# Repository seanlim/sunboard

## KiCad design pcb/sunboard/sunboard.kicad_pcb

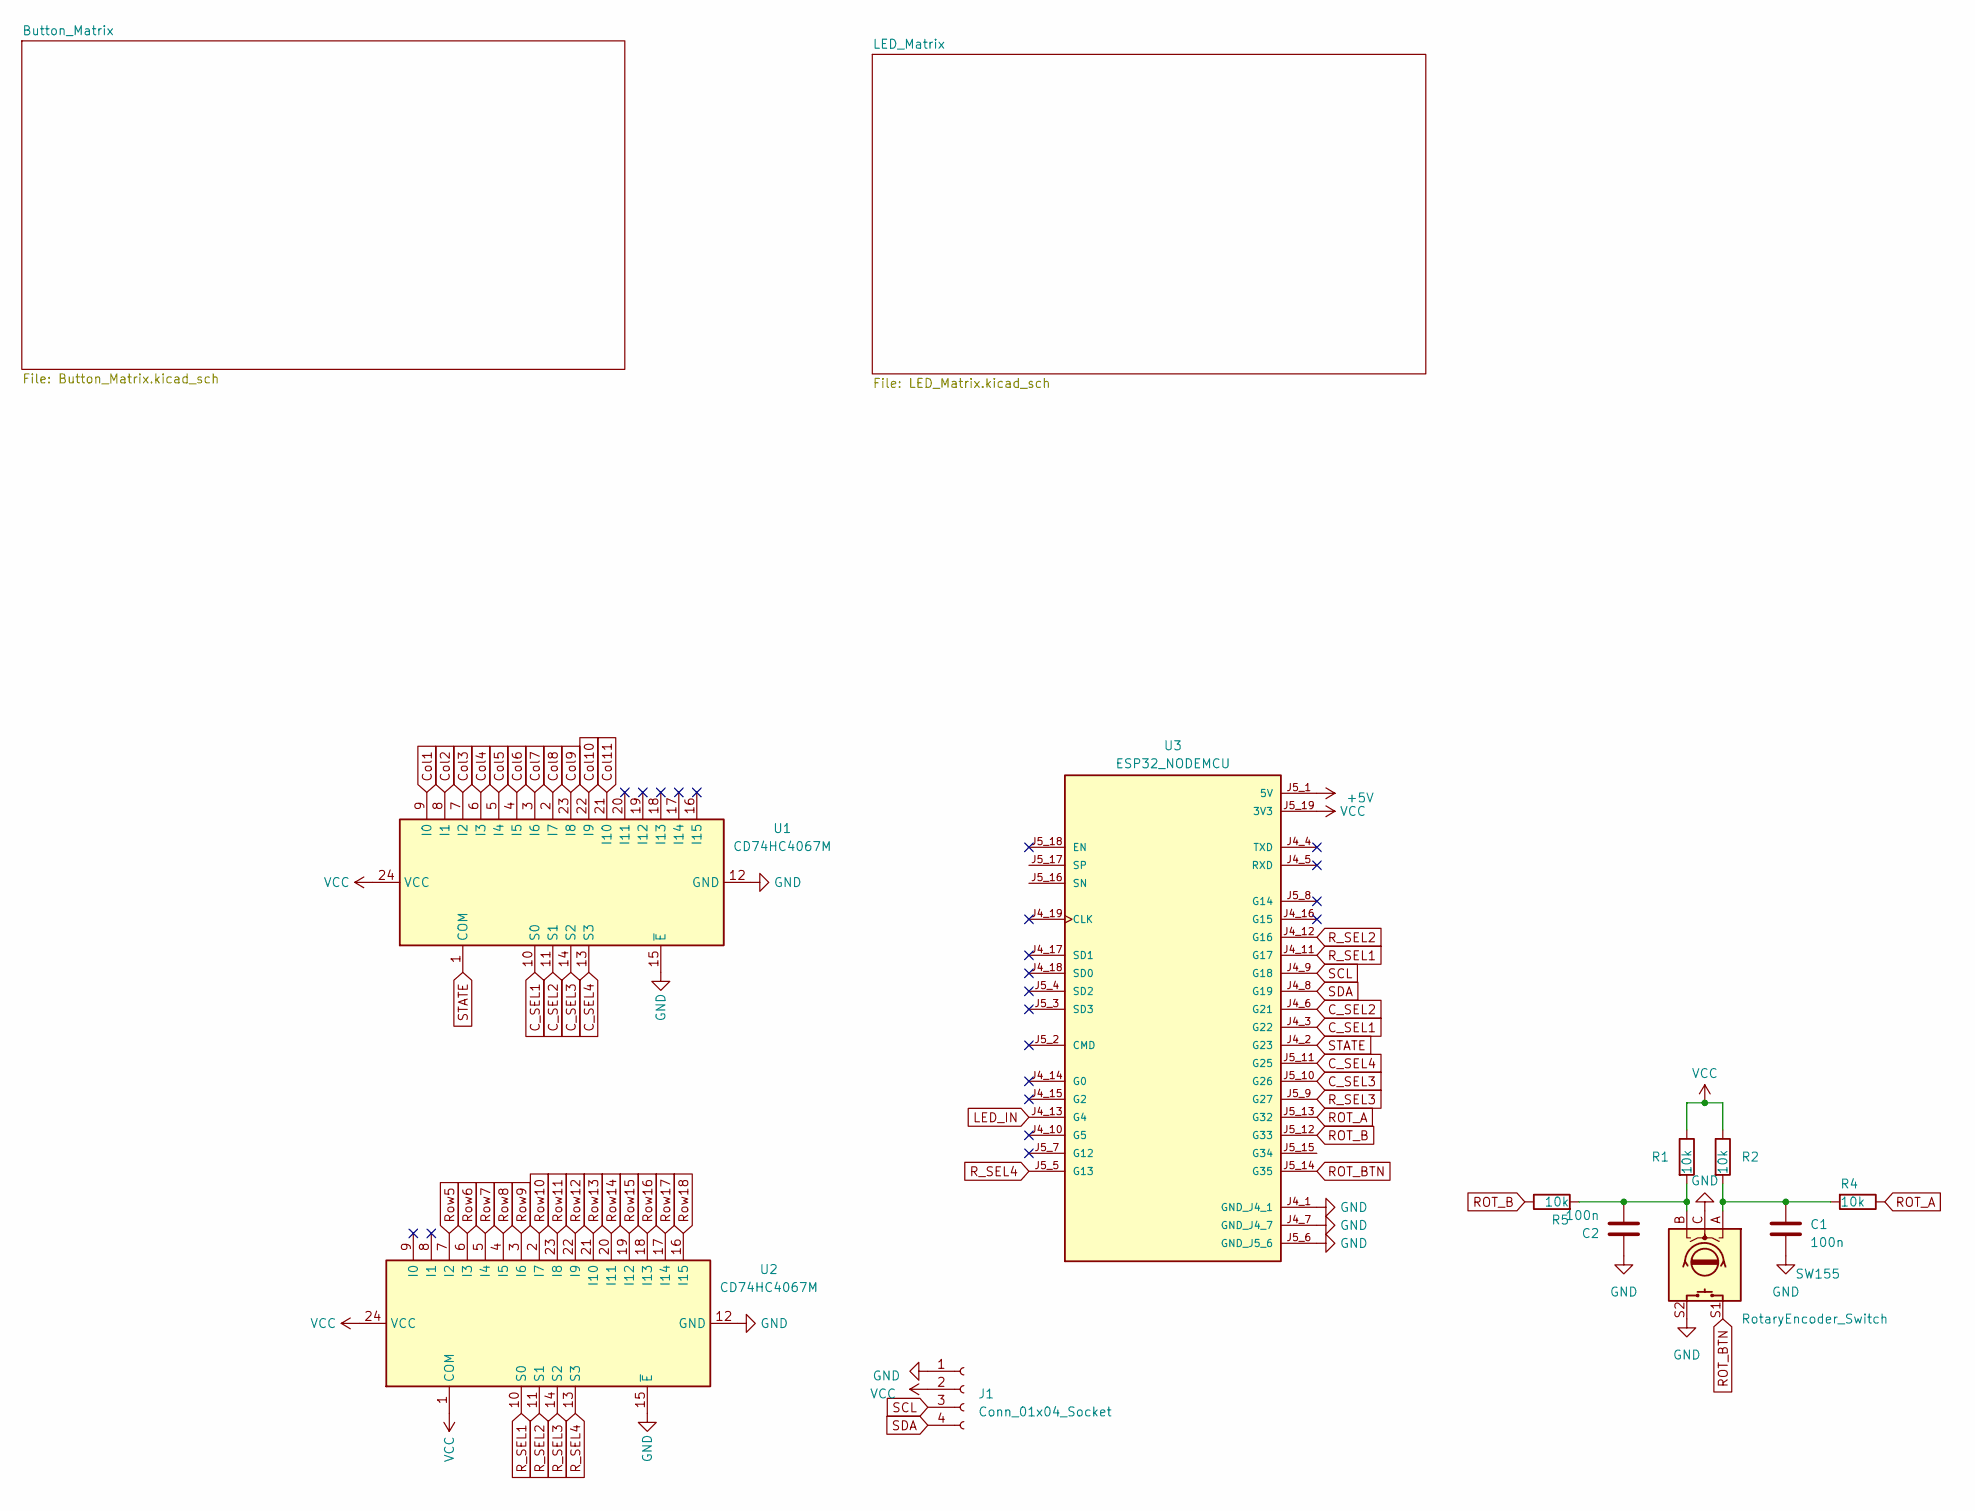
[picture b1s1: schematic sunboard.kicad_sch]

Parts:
C1, C2: 100n; C_0805_2012Metric; JLCPCB Part # C28233
J1: Conn_01x04_Socket; PinSocket_1x04_P2.54mm_Vertical
R1, R2, R4, R5: 10k; R_0805_2012Metric; JLCPCB Part # C17414
SW155: RotaryEncoder_Switch; RotaryEncoder_Alps_EC12E-Switch_Vertical_H20mm
U1, U2: CD74HC4067M; SOIC-24W_7.5x15.4mm_P1.27mm; JLCPCB Part # C496123
U3: ESP32_NODEMCU; MODULE_ESP32_NODEMCU

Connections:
+5V: U3.J5_1 (5V); also elsewhere on the board
C_SEL1: U1.14 (S2), U3.J5_10 (G26)
C_SEL2: U1.13 (S3), U3.J5_11 (G25)
C_SEL3: U1.10 (S0), U3.J4_3 (G22)
C_SEL4: U1.11 (S1), U3.J4_6 (G21)
Col1: U1.9 (I0); also elsewhere on the board
Col2: U1.8 (I1); also elsewhere on the board
Col3: U1.7 (I2); also elsewhere on the board
Col4: U1.6 (I3); also elsewhere on the board
Col5: U1.5 (I4); also elsewhere on the board
Col6: U1.4 (I5); also elsewhere on the board
Col7: U1.3 (I6); also elsewhere on the board
Col8: U1.2 (I7); also elsewhere on the board
Col9: U1.23 (I8); also elsewhere on the board
Col10: U1.22 (I9); also elsewhere on the board
Col11: U1.21 (I10); also elsewhere on the board
GND: C1.2, C2.1, J1.1, SW155.C, SW155.S2, U1.12 (GND), U1.15 (~E), U2.12 (GND), U2.15 (~E), U3.J4_1 (GND_J4_1), U3.J4_7 (GND_J4_7), U3.J5_6 (GND_J5_6); also elsewhere on the board
LED_IN: U3.J4_13 (G4); also elsewhere on the board
unnamed: C1.1, R2.2, R4.2, SW155.A
unnamed: C2.2, R1.2, R5.2, SW155.B
ROT_A: R4.1, U3.J5_13 (G32)
ROT_B: R5.1, U3.J5_12 (G33)
ROT_BTN: SW155.S1, U3.J5_14 (G35)
R_SEL1: U2.10 (S0), U3.J4_11 (G17)
R_SEL2: U2.11 (S1), U3.J4_12 (G16)
R_SEL3: U2.14 (S2), U3.J5_9 (G27)
R_SEL4: U2.13 (S3), U3.J5_5 (G13)
Row5: U2.7 (I2); also elsewhere on the board
Row6: U2.6 (I3); also elsewhere on the board
Row7: U2.5 (I4); also elsewhere on the board
Row8: U2.4 (I5); also elsewhere on the board
Row9: U2.3 (I6); also elsewhere on the board
Row10: U2.2 (I7); also elsewhere on the board
Row11: U2.23 (I8); also elsewhere on the board
Row12: U2.22 (I9); also elsewhere on the board
Row13: U2.21 (I10); also elsewhere on the board
Row14: U2.20 (I11); also elsewhere on the board
Row15: U2.19 (I12); also elsewhere on the board
Row16: U2.18 (I13); also elsewhere on the board
Row17: U2.17 (I14); also elsewhere on the board
Row18: U2.16 (I15); also elsewhere on the board
SCL: J1.3, U3.J4_9 (G18)
SDA: J1.4, U3.J4_8 (G19)
STATE: U1.1 (COM), U3.J4_2 (G23)
VCC: J1.2, R1.1, R2.1, U1.24 (VCC), U2.1 (COM), U2.24 (VCC), U3.J5_19 (3V3)

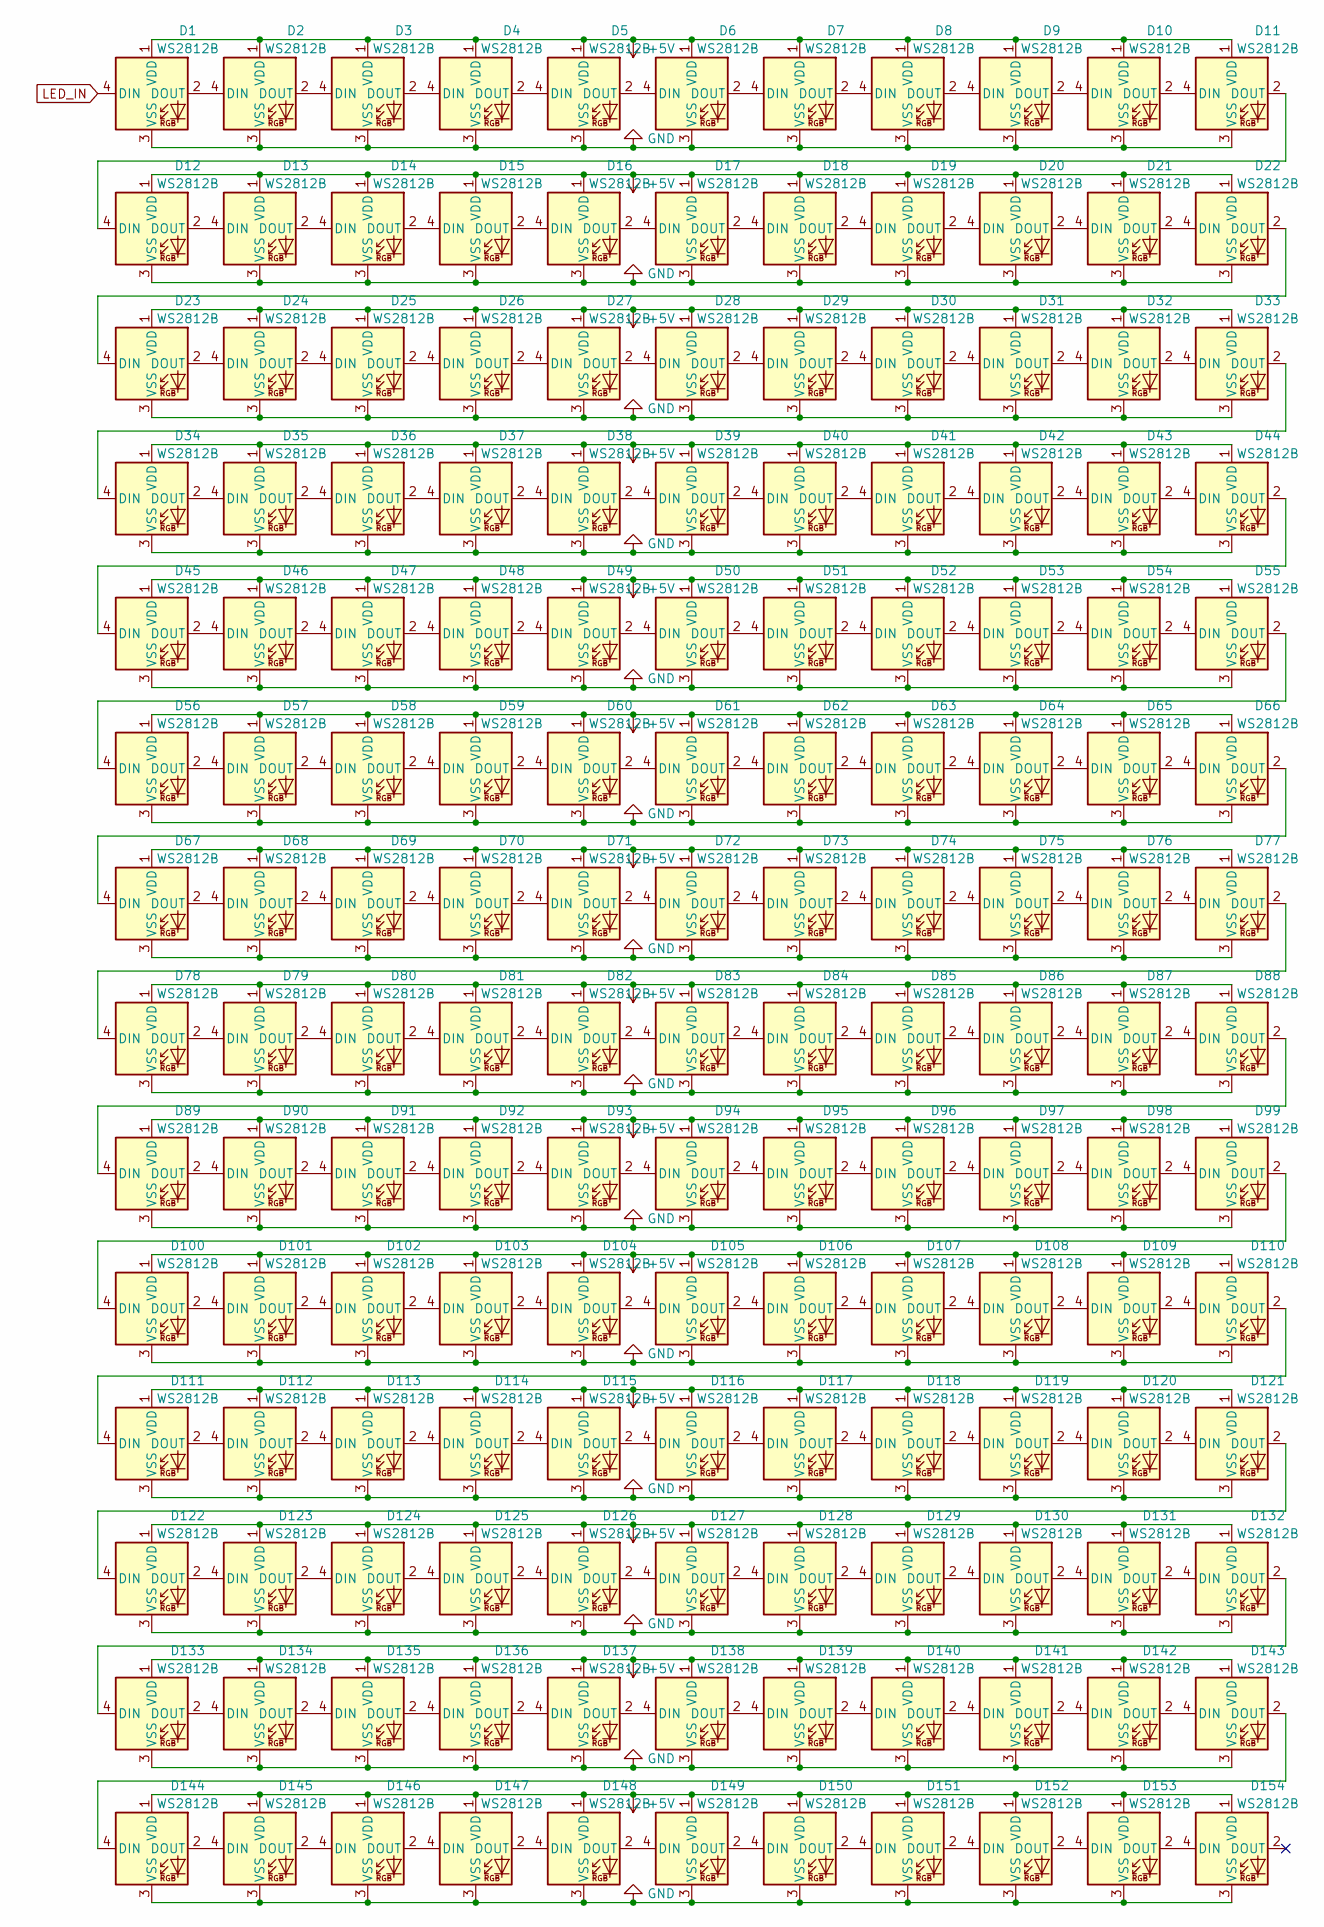
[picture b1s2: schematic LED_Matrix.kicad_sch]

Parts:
D1, D2, D3, D4, D5, D6, D7, D8, D9, D10, D11, D12, D13, D14, D15, D16, D17, D18, D19, D20, D21, D22, D23, D24, D25, D26, D27, D28, D29, D30, D31, D32, D33, D34, D35, D36, D37, D38, D39, D40, D41, D42, D43, D44, D45, D46, D47, D48, D49, D50, D51, D52, D53, D54, D55, D56, D57, D58, D59, D60, D61, D62, D63, D64, D65, D66, D67, D68, D69, D70, D71, D72, D73, D74, D75, D76, D77, D78, D79, D80, D81, D82, D83, D84, D85, D86, D87, D88, D89, D90, D91, D92, D93, D94, D95, D96, D97, D98, D99, D100, D101, D102, D103, D104, D105, D106, D107, D108, D109, D110, D111, D112, D113, D114, D115, D116, D117, D118, D119, D120, D121, D122, D123, D124, D125, D126, D127, D128, D129, D130, D131, D132, D133, D134, D135, D136, D137, D138, D139, D140, D141, D142, D143, D144, D145, D146, D147, D148, D149, D150, D151, D152, D153, D154: WS2812B; LED_WS2812B_PLCC4_5.0x5.0mm_P3.2mm; JLCPCB Part # C2843785

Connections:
+5V: D1.1 (VDD), D2.1 (VDD), D3.1 (VDD), D4.1 (VDD), D5.1 (VDD), D6.1 (VDD), D7.1 (VDD), D8.1 (VDD), D9.1 (VDD), D10.1 (VDD), D11.1 (VDD), D12.1 (VDD), D13.1 (VDD), D14.1 (VDD), D15.1 (VDD), D16.1 (VDD), D17.1 (VDD), D18.1 (VDD), D19.1 (VDD), D20.1 (VDD), D21.1 (VDD), D22.1 (VDD), D23.1 (VDD), D24.1 (VDD), D25.1 (VDD), D26.1 (VDD), D27.1 (VDD), D28.1 (VDD), D29.1 (VDD), D30.1 (VDD), D31.1 (VDD), D32.1 (VDD), D33.1 (VDD), D34.1 (VDD), D35.1 (VDD), D36.1 (VDD), D37.1 (VDD), D38.1 (VDD), D39.1 (VDD), D40.1 (VDD), D41.1 (VDD), D42.1 (VDD), D43.1 (VDD), D44.1 (VDD), D45.1 (VDD), D46.1 (VDD), D47.1 (VDD), D48.1 (VDD), D49.1 (VDD), D50.1 (VDD), D51.1 (VDD), D52.1 (VDD), D53.1 (VDD), D54.1 (VDD), D55.1 (VDD), D56.1 (VDD), D57.1 (VDD), D58.1 (VDD), D59.1 (VDD), D60.1 (VDD), D61.1 (VDD), D62.1 (VDD), D63.1 (VDD), D64.1 (VDD), D65.1 (VDD), D66.1 (VDD), D67.1 (VDD), D68.1 (VDD), D69.1 (VDD), D70.1 (VDD), D71.1 (VDD), D72.1 (VDD), D73.1 (VDD), D74.1 (VDD), D75.1 (VDD), D76.1 (VDD), D77.1 (VDD), D78.1 (VDD), D79.1 (VDD), D80.1 (VDD), D81.1 (VDD), D82.1 (VDD), D83.1 (VDD), D84.1 (VDD), D85.1 (VDD), D86.1 (VDD), D87.1 (VDD), D88.1 (VDD), D89.1 (VDD), D90.1 (VDD), D91.1 (VDD), D92.1 (VDD), D93.1 (VDD), D94.1 (VDD), D95.1 (VDD), D96.1 (VDD), D97.1 (VDD), D98.1 (VDD), D99.1 (VDD), D100.1 (VDD), D101.1 (VDD), D102.1 (VDD), D103.1 (VDD), D104.1 (VDD), D105.1 (VDD), D106.1 (VDD), D107.1 (VDD), D108.1 (VDD), D109.1 (VDD), D110.1 (VDD), D111.1 (VDD), D112.1 (VDD), D113.1 (VDD), D114.1 (VDD), D115.1 (VDD), D116.1 (VDD), D117.1 (VDD), D118.1 (VDD), D119.1 (VDD), D120.1 (VDD), D121.1 (VDD), D122.1 (VDD), D123.1 (VDD), D124.1 (VDD), D125.1 (VDD), D126.1 (VDD), D127.1 (VDD), D128.1 (VDD), D129.1 (VDD), D130.1 (VDD), D131.1 (VDD), D132.1 (VDD), D133.1 (VDD), D134.1 (VDD), D135.1 (VDD), D136.1 (VDD), D137.1 (VDD), D138.1 (VDD), D139.1 (VDD), D140.1 (VDD), D141.1 (VDD), D142.1 (VDD), D143.1 (VDD), D144.1 (VDD), D145.1 (VDD), D146.1 (VDD), D147.1 (VDD), D148.1 (VDD), D149.1 (VDD), D150.1 (VDD), D151.1 (VDD), D152.1 (VDD), D153.1 (VDD), D154.1 (VDD); also elsewhere on the board
GND: D1.3 (VSS), D2.3 (VSS), D3.3 (VSS), D4.3 (VSS), D5.3 (VSS), D6.3 (VSS), D7.3 (VSS), D8.3 (VSS), D9.3 (VSS), D10.3 (VSS), D11.3 (VSS), D12.3 (VSS), D13.3 (VSS), D14.3 (VSS), D15.3 (VSS), D16.3 (VSS), D17.3 (VSS), D18.3 (VSS), D19.3 (VSS), D20.3 (VSS), D21.3 (VSS), D22.3 (VSS), D23.3 (VSS), D24.3 (VSS), D25.3 (VSS), D26.3 (VSS), D27.3 (VSS), D28.3 (VSS), D29.3 (VSS), D30.3 (VSS), D31.3 (VSS), D32.3 (VSS), D33.3 (VSS), D34.3 (VSS), D35.3 (VSS), D36.3 (VSS), D37.3 (VSS), D38.3 (VSS), D39.3 (VSS), D40.3 (VSS), D41.3 (VSS), D42.3 (VSS), D43.3 (VSS), D44.3 (VSS), D45.3 (VSS), D46.3 (VSS), D47.3 (VSS), D48.3 (VSS), D49.3 (VSS), D50.3 (VSS), D51.3 (VSS), D52.3 (VSS), D53.3 (VSS), D54.3 (VSS), D55.3 (VSS), D56.3 (VSS), D57.3 (VSS), D58.3 (VSS), D59.3 (VSS), D60.3 (VSS), D61.3 (VSS), D62.3 (VSS), D63.3 (VSS), D64.3 (VSS), D65.3 (VSS), D66.3 (VSS), D67.3 (VSS), D68.3 (VSS), D69.3 (VSS), D70.3 (VSS), D71.3 (VSS), D72.3 (VSS), D73.3 (VSS), D74.3 (VSS), D75.3 (VSS), D76.3 (VSS), D77.3 (VSS), D78.3 (VSS), D79.3 (VSS), D80.3 (VSS), D81.3 (VSS), D82.3 (VSS), D83.3 (VSS), D84.3 (VSS), D85.3 (VSS), D86.3 (VSS), D87.3 (VSS), D88.3 (VSS), D89.3 (VSS), D90.3 (VSS), D91.3 (VSS), D92.3 (VSS), D93.3 (VSS), D94.3 (VSS), D95.3 (VSS), D96.3 (VSS), D97.3 (VSS), D98.3 (VSS), D99.3 (VSS), D100.3 (VSS), D101.3 (VSS), D102.3 (VSS), D103.3 (VSS), D104.3 (VSS), D105.3 (VSS), D106.3 (VSS), D107.3 (VSS), D108.3 (VSS), D109.3 (VSS), D110.3 (VSS), D111.3 (VSS), D112.3 (VSS), D113.3 (VSS), D114.3 (VSS), D115.3 (VSS), D116.3 (VSS), D117.3 (VSS), D118.3 (VSS), D119.3 (VSS), D120.3 (VSS), D121.3 (VSS), D122.3 (VSS), D123.3 (VSS), D124.3 (VSS), D125.3 (VSS), D126.3 (VSS), D127.3 (VSS), D128.3 (VSS), D129.3 (VSS), D130.3 (VSS), D131.3 (VSS), D132.3 (VSS), D133.3 (VSS), D134.3 (VSS), D135.3 (VSS), D136.3 (VSS), D137.3 (VSS), D138.3 (VSS), D139.3 (VSS), D140.3 (VSS), D141.3 (VSS), D142.3 (VSS), D143.3 (VSS), D144.3 (VSS), D145.3 (VSS), D146.3 (VSS), D147.3 (VSS), D148.3 (VSS), D149.3 (VSS), D150.3 (VSS), D151.3 (VSS), D152.3 (VSS), D153.3 (VSS), D154.3 (VSS); also elsewhere on the board
LED_IN: D1.4 (DIN); also elsewhere on the board
unnamed: D1.2 (DOUT), D2.4 (DIN)
unnamed: D2.2 (DOUT), D3.4 (DIN)
unnamed: D3.2 (DOUT), D4.4 (DIN)
unnamed: D4.2 (DOUT), D5.4 (DIN)
unnamed: D5.2 (DOUT), D6.4 (DIN)
unnamed: D6.2 (DOUT), D7.4 (DIN)
unnamed: D7.2 (DOUT), D8.4 (DIN)
unnamed: D8.2 (DOUT), D9.4 (DIN)
unnamed: D9.2 (DOUT), D10.4 (DIN)
unnamed: D10.2 (DOUT), D11.4 (DIN)
unnamed: D11.2 (DOUT), D12.4 (DIN)
unnamed: D12.2 (DOUT), D13.4 (DIN)
unnamed: D13.2 (DOUT), D14.4 (DIN)
unnamed: D14.2 (DOUT), D15.4 (DIN)
unnamed: D15.2 (DOUT), D16.4 (DIN)
unnamed: D16.2 (DOUT), D17.4 (DIN)
unnamed: D17.2 (DOUT), D18.4 (DIN)
unnamed: D18.2 (DOUT), D19.4 (DIN)
unnamed: D19.2 (DOUT), D20.4 (DIN)
unnamed: D20.2 (DOUT), D21.4 (DIN)
unnamed: D21.2 (DOUT), D22.4 (DIN)
unnamed: D22.2 (DOUT), D23.4 (DIN)
unnamed: D23.2 (DOUT), D24.4 (DIN)
unnamed: D24.2 (DOUT), D25.4 (DIN)
unnamed: D25.2 (DOUT), D26.4 (DIN)
unnamed: D26.2 (DOUT), D27.4 (DIN)
unnamed: D27.2 (DOUT), D28.4 (DIN)
unnamed: D28.2 (DOUT), D29.4 (DIN)
unnamed: D29.2 (DOUT), D30.4 (DIN)
unnamed: D30.2 (DOUT), D31.4 (DIN)
unnamed: D31.2 (DOUT), D32.4 (DIN)
unnamed: D32.2 (DOUT), D33.4 (DIN)
unnamed: D33.2 (DOUT), D34.4 (DIN)
unnamed: D34.2 (DOUT), D35.4 (DIN)
unnamed: D35.2 (DOUT), D36.4 (DIN)
unnamed: D36.2 (DOUT), D37.4 (DIN)
unnamed: D37.2 (DOUT), D38.4 (DIN)
unnamed: D38.2 (DOUT), D39.4 (DIN)
unnamed: D39.2 (DOUT), D40.4 (DIN)
unnamed: D40.2 (DOUT), D41.4 (DIN)
unnamed: D41.2 (DOUT), D42.4 (DIN)
unnamed: D42.2 (DOUT), D43.4 (DIN)
unnamed: D43.2 (DOUT), D44.4 (DIN)
unnamed: D44.2 (DOUT), D45.4 (DIN)
unnamed: D45.2 (DOUT), D46.4 (DIN)
unnamed: D46.2 (DOUT), D47.4 (DIN)
unnamed: D47.2 (DOUT), D48.4 (DIN)
unnamed: D48.2 (DOUT), D49.4 (DIN)
unnamed: D49.2 (DOUT), D50.4 (DIN)
unnamed: D50.2 (DOUT), D51.4 (DIN)
unnamed: D51.2 (DOUT), D52.4 (DIN)
unnamed: D52.2 (DOUT), D53.4 (DIN)
unnamed: D53.2 (DOUT), D54.4 (DIN)
unnamed: D54.2 (DOUT), D55.4 (DIN)
unnamed: D55.2 (DOUT), D56.4 (DIN)
unnamed: D56.2 (DOUT), D57.4 (DIN)
unnamed: D57.2 (DOUT), D58.4 (DIN)
unnamed: D58.2 (DOUT), D59.4 (DIN)
unnamed: D59.2 (DOUT), D60.4 (DIN)
unnamed: D60.2 (DOUT), D61.4 (DIN)
unnamed: D61.2 (DOUT), D62.4 (DIN)
unnamed: D62.2 (DOUT), D63.4 (DIN)
unnamed: D63.2 (DOUT), D64.4 (DIN)
unnamed: D64.2 (DOUT), D65.4 (DIN)
unnamed: D65.2 (DOUT), D66.4 (DIN)
unnamed: D66.2 (DOUT), D67.4 (DIN)
unnamed: D67.2 (DOUT), D68.4 (DIN)
unnamed: D68.2 (DOUT), D69.4 (DIN)
unnamed: D69.2 (DOUT), D70.4 (DIN)
unnamed: D70.2 (DOUT), D71.4 (DIN)
unnamed: D71.2 (DOUT), D72.4 (DIN)
unnamed: D72.2 (DOUT), D73.4 (DIN)
unnamed: D73.2 (DOUT), D74.4 (DIN)
unnamed: D74.2 (DOUT), D75.4 (DIN)
unnamed: D75.2 (DOUT), D76.4 (DIN)
unnamed: D76.2 (DOUT), D77.4 (DIN)
unnamed: D77.2 (DOUT), D78.4 (DIN)
unnamed: D78.2 (DOUT), D79.4 (DIN)
unnamed: D79.2 (DOUT), D80.4 (DIN)
unnamed: D80.2 (DOUT), D81.4 (DIN)
unnamed: D81.2 (DOUT), D82.4 (DIN)
unnamed: D82.2 (DOUT), D83.4 (DIN)
unnamed: D83.2 (DOUT), D84.4 (DIN)
unnamed: D84.2 (DOUT), D85.4 (DIN)
unnamed: D85.2 (DOUT), D86.4 (DIN)
unnamed: D86.2 (DOUT), D87.4 (DIN)
unnamed: D87.2 (DOUT), D88.4 (DIN)
unnamed: D88.2 (DOUT), D89.4 (DIN)
unnamed: D89.2 (DOUT), D90.4 (DIN)
unnamed: D90.2 (DOUT), D91.4 (DIN)
unnamed: D91.2 (DOUT), D92.4 (DIN)
unnamed: D92.2 (DOUT), D93.4 (DIN)
unnamed: D93.2 (DOUT), D94.4 (DIN)
unnamed: D94.2 (DOUT), D95.4 (DIN)
unnamed: D95.2 (DOUT), D96.4 (DIN)
unnamed: D96.2 (DOUT), D97.4 (DIN)
unnamed: D97.2 (DOUT), D98.4 (DIN)
unnamed: D98.2 (DOUT), D99.4 (DIN)
unnamed: D99.2 (DOUT), D100.4 (DIN)
unnamed: D100.2 (DOUT), D101.4 (DIN)
unnamed: D101.2 (DOUT), D102.4 (DIN)
unnamed: D102.2 (DOUT), D103.4 (DIN)
unnamed: D103.2 (DOUT), D104.4 (DIN)
unnamed: D104.2 (DOUT), D105.4 (DIN)
unnamed: D105.2 (DOUT), D106.4 (DIN)
unnamed: D106.2 (DOUT), D107.4 (DIN)
unnamed: D107.2 (DOUT), D108.4 (DIN)
unnamed: D108.2 (DOUT), D109.4 (DIN)
unnamed: D109.2 (DOUT), D110.4 (DIN)
unnamed: D110.2 (DOUT), D111.4 (DIN)
unnamed: D111.2 (DOUT), D112.4 (DIN)
unnamed: D112.2 (DOUT), D113.4 (DIN)
unnamed: D113.2 (DOUT), D114.4 (DIN)
unnamed: D114.2 (DOUT), D115.4 (DIN)
unnamed: D115.2 (DOUT), D116.4 (DIN)
unnamed: D116.2 (DOUT), D117.4 (DIN)
unnamed: D117.2 (DOUT), D118.4 (DIN)
unnamed: D118.2 (DOUT), D119.4 (DIN)
unnamed: D119.2 (DOUT), D120.4 (DIN)
unnamed: D120.2 (DOUT), D121.4 (DIN)
unnamed: D121.2 (DOUT), D122.4 (DIN)
unnamed: D122.2 (DOUT), D123.4 (DIN)
unnamed: D123.2 (DOUT), D124.4 (DIN)
unnamed: D124.2 (DOUT), D125.4 (DIN)
unnamed: D125.2 (DOUT), D126.4 (DIN)
unnamed: D126.2 (DOUT), D127.4 (DIN)
unnamed: D127.2 (DOUT), D128.4 (DIN)
unnamed: D128.2 (DOUT), D129.4 (DIN)
unnamed: D129.2 (DOUT), D130.4 (DIN)
unnamed: D130.2 (DOUT), D131.4 (DIN)
unnamed: D131.2 (DOUT), D132.4 (DIN)
unnamed: D132.2 (DOUT), D133.4 (DIN)
unnamed: D133.2 (DOUT), D134.4 (DIN)
unnamed: D134.2 (DOUT), D135.4 (DIN)
unnamed: D135.2 (DOUT), D136.4 (DIN)
unnamed: D136.2 (DOUT), D137.4 (DIN)
unnamed: D137.2 (DOUT), D138.4 (DIN)
unnamed: D138.2 (DOUT), D139.4 (DIN)
unnamed: D139.2 (DOUT), D140.4 (DIN)
unnamed: D140.2 (DOUT), D141.4 (DIN)
unnamed: D141.2 (DOUT), D142.4 (DIN)
unnamed: D142.2 (DOUT), D143.4 (DIN)
unnamed: D143.2 (DOUT), D144.4 (DIN)
unnamed: D144.2 (DOUT), D145.4 (DIN)
unnamed: D145.2 (DOUT), D146.4 (DIN)
unnamed: D146.2 (DOUT), D147.4 (DIN)
unnamed: D147.2 (DOUT), D148.4 (DIN)
unnamed: D148.2 (DOUT), D149.4 (DIN)
unnamed: D149.2 (DOUT), D150.4 (DIN)
unnamed: D150.2 (DOUT), D151.4 (DIN)
unnamed: D151.2 (DOUT), D152.4 (DIN)
unnamed: D152.2 (DOUT), D153.4 (DIN)
unnamed: D153.2 (DOUT), D154.4 (DIN)

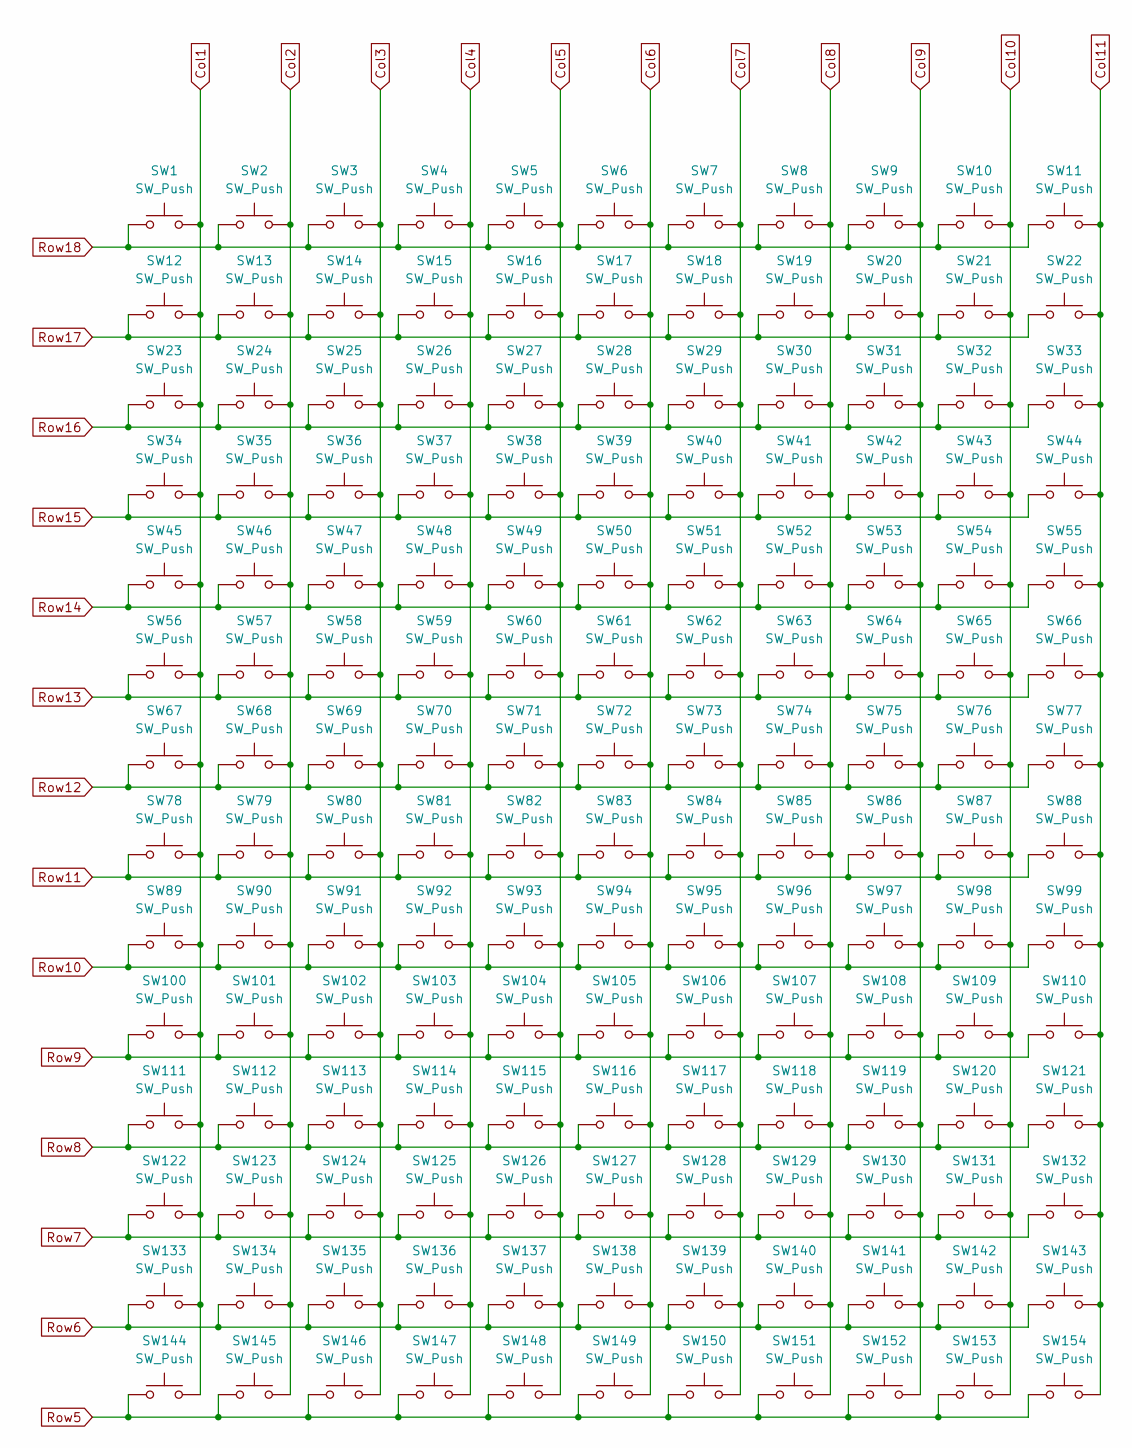
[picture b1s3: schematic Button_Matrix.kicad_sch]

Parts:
SW1, SW2, SW3, SW4, SW5, SW6, SW7, SW8, SW9, SW10, SW11, SW12, SW13, SW14, SW15, SW16, SW17, SW18, SW19, SW20, SW21, SW22, SW23, SW24, SW25, SW26, SW27, SW28, SW29, SW30, SW31, SW32, SW33, SW34, SW35, SW36, SW37, SW38, SW39, SW40, SW41, SW42, SW43, SW44, SW45, SW46, SW47, SW48, SW49, SW50, SW51, SW52, SW53, SW54, SW55, SW56, SW57, SW58, SW59, SW60, SW61, SW62, SW63, SW64, SW65, SW66, SW67, SW68, SW69, SW70, SW71, SW72, SW73, SW74, SW75, SW76, SW77, SW78, SW79, SW80, SW81, SW82, SW83, SW84, SW85, SW86, SW87, SW88, SW89, SW90, SW91, SW92, SW93, SW94, SW95, SW96, SW97, SW98, SW99, SW100, SW101, SW102, SW103, SW104, SW105, SW106, SW107, SW108, SW109, SW110, SW111, SW112, SW113, SW114, SW115, SW116, SW117, SW118, SW119, SW120, SW121, SW122, SW123, SW124, SW125, SW126, SW127, SW128, SW129, SW130, SW131, SW132, SW133, SW134, SW135, SW136, SW137, SW138, SW139, SW140, SW141, SW142, SW143, SW144, SW145, SW146, SW147, SW148, SW149, SW150, SW151, SW152, SW153, SW154: SW_Push; SW_Push_1P1T_NO_6x6mm_H9.5mm; JLCPCB Part # C455109

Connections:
Col1: SW1.2, SW12.2, SW23.2, SW34.2, SW45.2, SW56.2, SW67.2, SW78.2, SW89.2, SW100.2, SW111.2, SW122.2, SW133.2, SW144.2; also elsewhere on the board
Col2: SW2.2, SW13.2, SW24.2, SW35.2, SW46.2, SW57.2, SW68.2, SW79.2, SW90.2, SW101.2, SW112.2, SW123.2, SW134.2, SW145.2; also elsewhere on the board
Col3: SW3.2, SW14.2, SW25.2, SW36.2, SW47.2, SW58.2, SW69.2, SW80.2, SW91.2, SW102.2, SW113.2, SW124.2, SW135.2, SW146.2; also elsewhere on the board
Col4: SW4.2, SW15.2, SW26.2, SW37.2, SW48.2, SW59.2, SW70.2, SW81.2, SW92.2, SW103.2, SW114.2, SW125.2, SW136.2, SW147.2; also elsewhere on the board
Col5: SW5.2, SW16.2, SW27.2, SW38.2, SW49.2, SW60.2, SW71.2, SW82.2, SW93.2, SW104.2, SW115.2, SW126.2, SW137.2, SW148.2; also elsewhere on the board
Col6: SW6.2, SW17.2, SW28.2, SW39.2, SW50.2, SW61.2, SW72.2, SW83.2, SW94.2, SW105.2, SW116.2, SW127.2, SW138.2, SW149.2; also elsewhere on the board
Col7: SW7.2, SW18.2, SW29.2, SW40.2, SW51.2, SW62.2, SW73.2, SW84.2, SW95.2, SW106.2, SW117.2, SW128.2, SW139.2, SW150.2; also elsewhere on the board
Col8: SW8.2, SW19.2, SW30.2, SW41.2, SW52.2, SW63.2, SW74.2, SW85.2, SW96.2, SW107.2, SW118.2, SW129.2, SW140.2, SW151.2; also elsewhere on the board
Col9: SW9.2, SW20.2, SW31.2, SW42.2, SW53.2, SW64.2, SW75.2, SW86.2, SW97.2, SW108.2, SW119.2, SW130.2, SW141.2, SW152.2; also elsewhere on the board
Col10: SW10.2, SW21.2, SW32.2, SW43.2, SW54.2, SW65.2, SW76.2, SW87.2, SW98.2, SW109.2, SW120.2, SW131.2, SW142.2, SW153.2; also elsewhere on the board
Col11: SW11.2, SW22.2, SW33.2, SW44.2, SW55.2, SW66.2, SW77.2, SW88.2, SW99.2, SW110.2, SW121.2, SW132.2, SW143.2, SW154.2; also elsewhere on the board
Row5: SW144.1, SW145.1, SW146.1, SW147.1, SW148.1, SW149.1, SW150.1, SW151.1, SW152.1, SW153.1, SW154.1; also elsewhere on the board
Row6: SW133.1, SW134.1, SW135.1, SW136.1, SW137.1, SW138.1, SW139.1, SW140.1, SW141.1, SW142.1, SW143.1; also elsewhere on the board
Row7: SW122.1, SW123.1, SW124.1, SW125.1, SW126.1, SW127.1, SW128.1, SW129.1, SW130.1, SW131.1, SW132.1; also elsewhere on the board
Row8: SW111.1, SW112.1, SW113.1, SW114.1, SW115.1, SW116.1, SW117.1, SW118.1, SW119.1, SW120.1, SW121.1; also elsewhere on the board
Row9: SW100.1, SW101.1, SW102.1, SW103.1, SW104.1, SW105.1, SW106.1, SW107.1, SW108.1, SW109.1, SW110.1; also elsewhere on the board
Row10: SW89.1, SW90.1, SW91.1, SW92.1, SW93.1, SW94.1, SW95.1, SW96.1, SW97.1, SW98.1, SW99.1; also elsewhere on the board
Row11: SW78.1, SW79.1, SW80.1, SW81.1, SW82.1, SW83.1, SW84.1, SW85.1, SW86.1, SW87.1, SW88.1; also elsewhere on the board
Row12: SW67.1, SW68.1, SW69.1, SW70.1, SW71.1, SW72.1, SW73.1, SW74.1, SW75.1, SW76.1, SW77.1; also elsewhere on the board
Row13: SW56.1, SW57.1, SW58.1, SW59.1, SW60.1, SW61.1, SW62.1, SW63.1, SW64.1, SW65.1, SW66.1; also elsewhere on the board
Row14: SW45.1, SW46.1, SW47.1, SW48.1, SW49.1, SW50.1, SW51.1, SW52.1, SW53.1, SW54.1, SW55.1; also elsewhere on the board
Row15: SW34.1, SW35.1, SW36.1, SW37.1, SW38.1, SW39.1, SW40.1, SW41.1, SW42.1, SW43.1, SW44.1; also elsewhere on the board
Row16: SW23.1, SW24.1, SW25.1, SW26.1, SW27.1, SW28.1, SW29.1, SW30.1, SW31.1, SW32.1, SW33.1; also elsewhere on the board
Row17: SW12.1, SW13.1, SW14.1, SW15.1, SW16.1, SW17.1, SW18.1, SW19.1, SW20.1, SW21.1, SW22.1; also elsewhere on the board
Row18: SW1.1, SW2.1, SW3.1, SW4.1, SW5.1, SW6.1, SW7.1, SW8.1, SW9.1, SW10.1, SW11.1; also elsewhere on the board

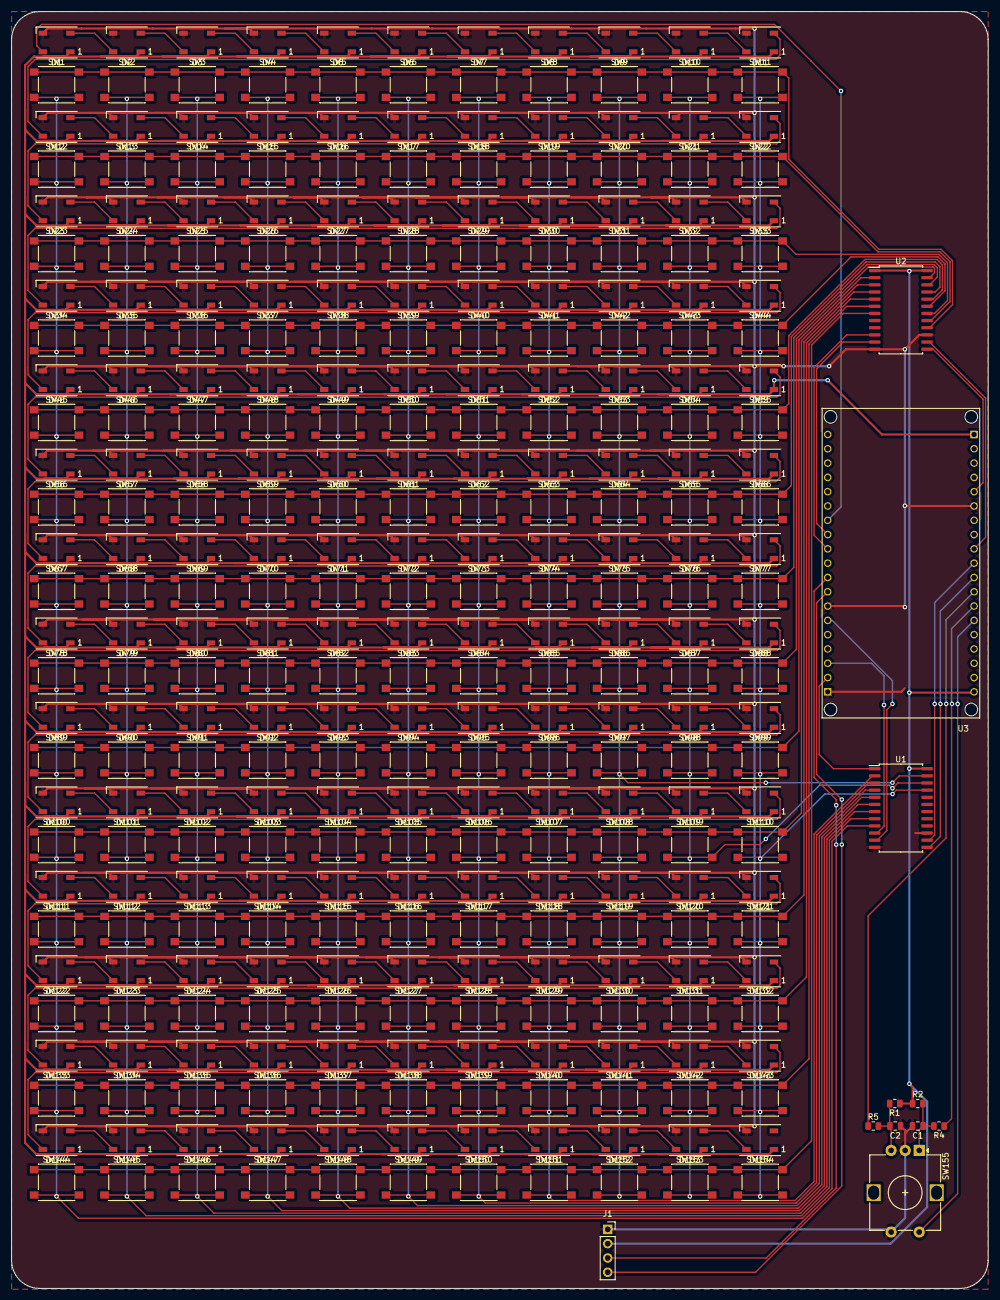
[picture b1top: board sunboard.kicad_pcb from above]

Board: 2 copper layers, 173.5 x 226.9 mm, 319 parts (0 on the bottom side), 198 nets.

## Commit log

2023-05-14 feat: add mock-moonboard
2023-05-14 feat: add mock layout
2023-05-28 feat: add 198 buttons
2023-05-28 feat: remove bottom 4 rows of buttons (footholds)
2023-05-28 feat: get basic POC for 8x8 out
2023-05-28 feat(pcb): migrate to subsheets
2023-05-28 add a README
2023-05-28 feat(pcb): remove led driver, layout main grid
2023-05-28 feat(pcb): add nets for rows and columns
2023-05-28 feat(pcb): add led driver
2023-05-28 feat(pcb): add esp32 deps
2023-05-28 initialise React Native app
2023-05-28 feat(pcb): update schematic to use 6x6 buttons
2023-05-28 feat(pcb): add 74hc4067 for mux/demux
    Now the board uses 74hc4067 for both mux / demux purposes. A surprisingly nice chip with both functionalities. Might use it for the lights also
2023-05-28 feat(pcb): add power netclass
2023-05-28 fea(pcb): route vcc
2023-05-28 feat(pcb): finish routing main
2023-05-28 feat(pcb): update design rules
2023-05-28 feat(pcb): finish routing main pcb
2023-05-28 feat(pcb): route gnd
2023-06-01 feat(pcb): finish routing pcb
2023-06-05 feat(pcb): add display
2023-06-13 feat: add base sunboard controller code
2023-06-14 feat(board): wip
2023-06-24 feat(board): testing code to check rows working
2023-06-24 feat(board): index column and row accurately
2023-06-24 feat(board): add more macros for printing
2023-06-24 feat(board): correctly light up pressed button
2023-06-24 fix existing app demo
2023-06-24 add constants file
2023-06-24 feat(pcb): rename some labels
2023-06-24 feat(board): split to seperate thread to read button states
2023-06-25 add react navigation, transmit value for default rout
2023-06-25 add stack navigator, move ble code out of App.tsx
2023-06-25 add BLEManager boilerplate
2023-06-25 add scan and transmit demo functionality
2023-06-25 feat(board): add ability to light up to moonboard
2023-06-25 feat(board): remove unneeded deps
2023-06-28 add 2016 routes
    using Git LFS https://git-lfs.com/
2023-06-29 feat(board): migrate to utility classes
2023-07-14 feat(board): wrapper around screen library
2023-07-20 wip screen code
2023-07-21 feat(board): push encoder
2023-07-21 feat(board): add screen
2023-07-21 add routes list
    wip convert holds to transmission format
2023-07-22 wip figure out hold number calculation
2023-07-23 fix route encoding
2023-07-23 update send format
2023-07-23 app: send route name, grade, and encoding
    * add routes list
    wip convert holds to transmission format
    * wip figure out hold number calculation
    * fix route encoding
    * update send format
2023-07-23 feat(board): store up to 10 routes wow!!!!!
2023-07-23 feat(board): connect to both moonboard and sunboard
